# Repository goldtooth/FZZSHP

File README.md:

View this project on [CADLAB.io](https://cadlab.io/project/1550). 

# FZZSHP

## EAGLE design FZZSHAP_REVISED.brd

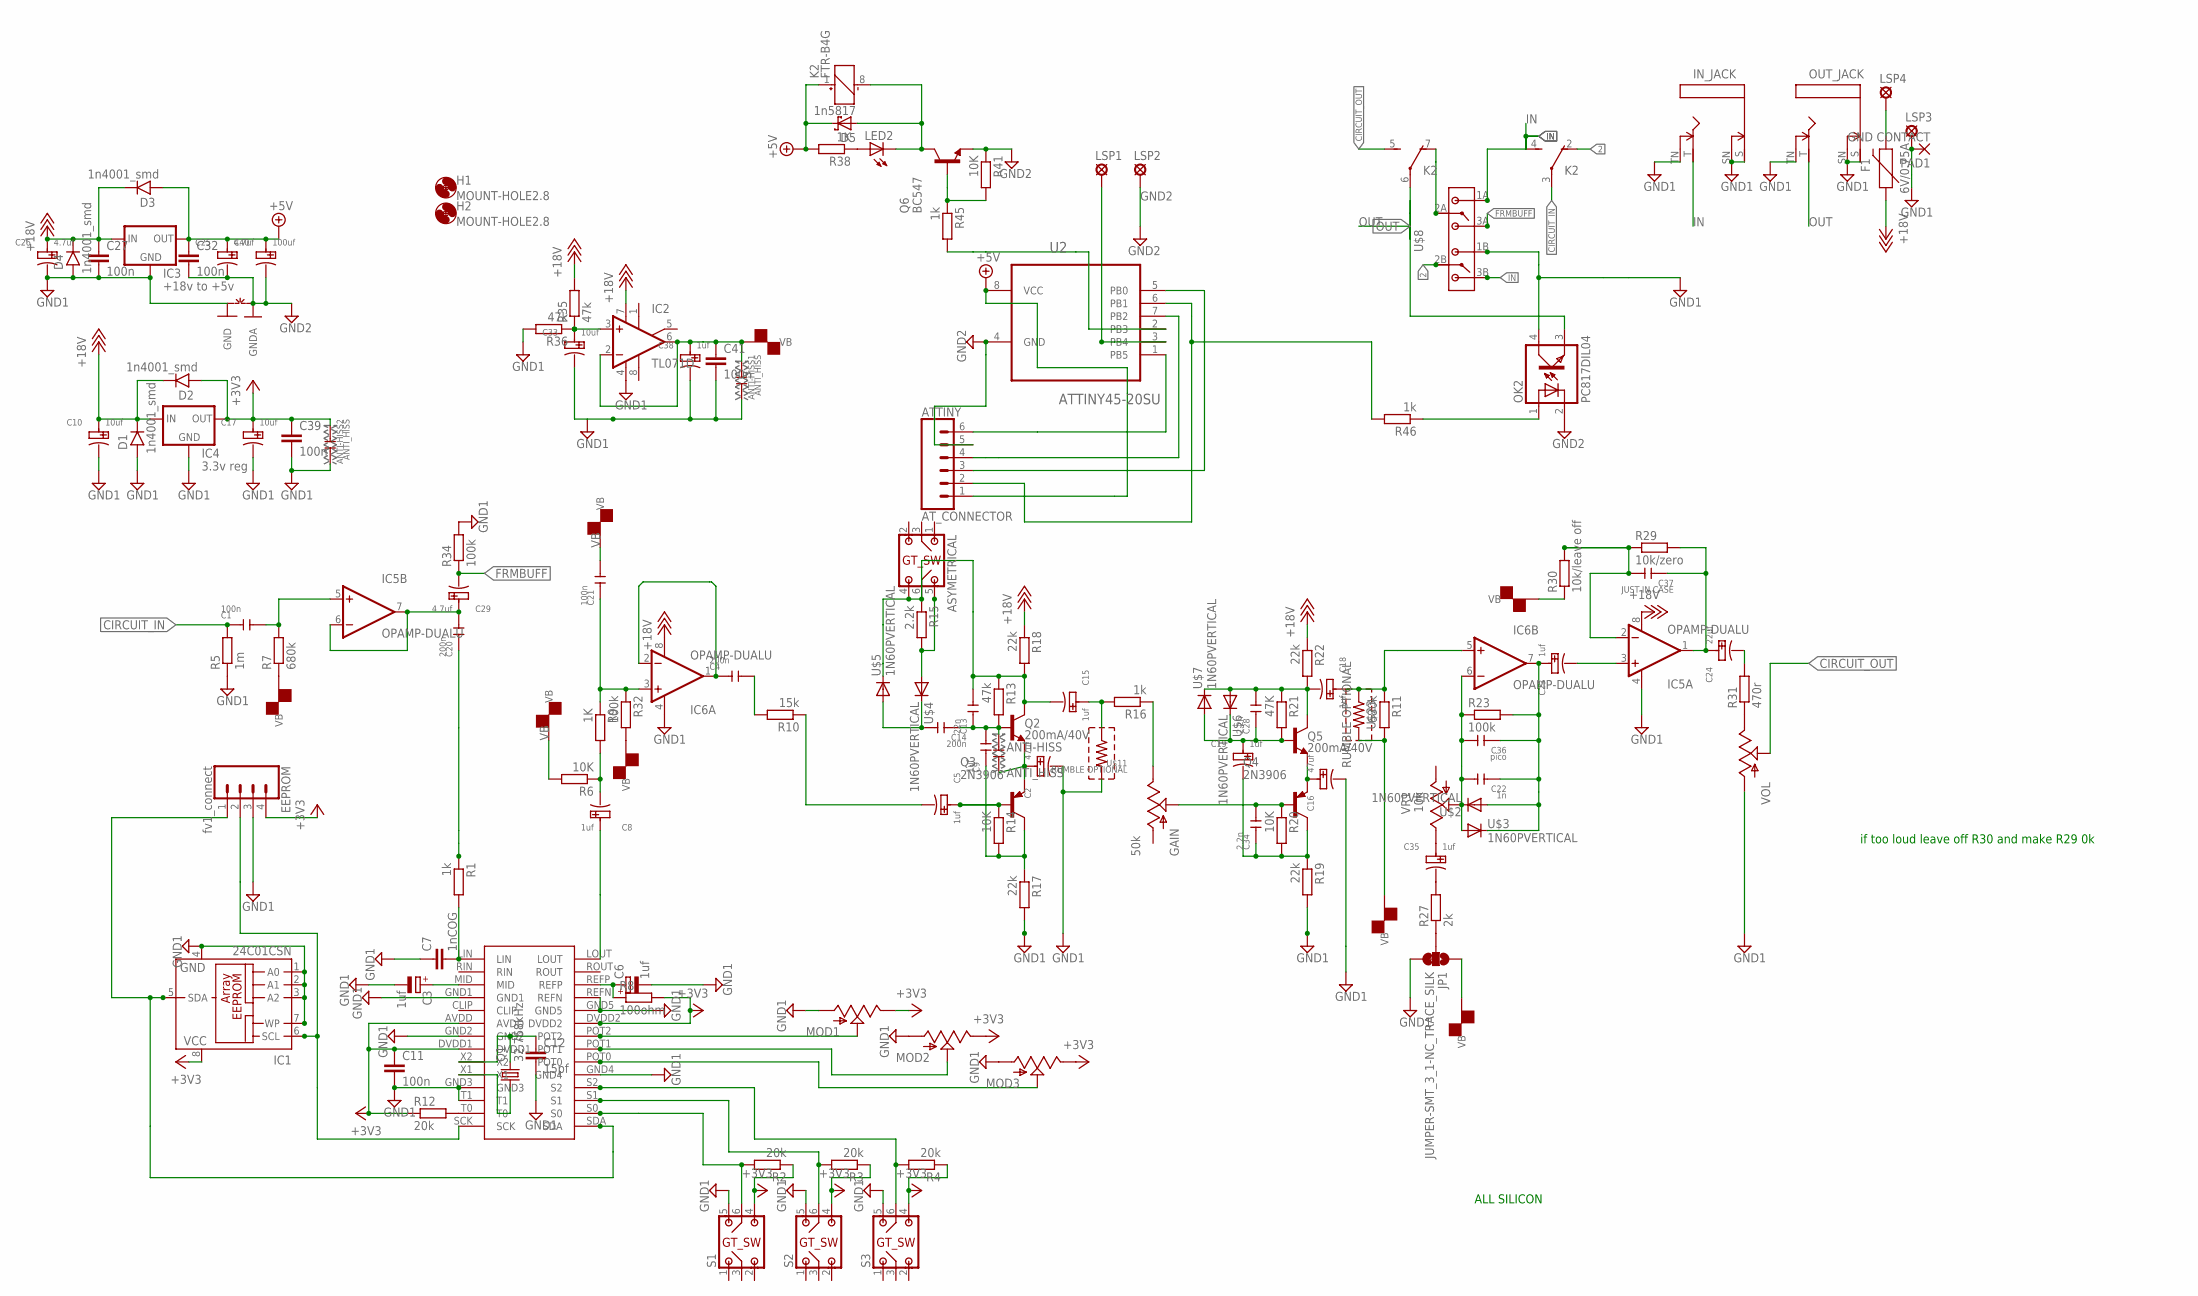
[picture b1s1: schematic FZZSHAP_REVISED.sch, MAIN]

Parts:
ANTI-HISS, ANTI-HISS1, ANTI-HISS2: ANTI_HISS; SMD_OPTIONAL
ASYMETRICAL: DP03SWPOT; DP-03
ATTINY: AT_CONNECTOR; 1X06_LONGPADS
C1, C21: 100n; CERAMIC-5MM
C2, C16: 47uf; PC-D5.3MM
C3, C6: 1uf; A/3216-18R
C4, C14, C20: 200n; CERAMIC-5MM
C5, C8, C15, C18, C19, C23, C35, C38: 1uf; PC-D5.3MM
C7: 1nCOG; C0805K
C9: 1uf; CERAMIC-5MM
C10, C17, C33: 10uf; PC-D5.3MM
C11: 100n; C0805
C12: 15pf; C0805
C13: 22n; CERAMIC-5MM
C22: 1n; CERAMIC-5MM
C24: 22uf; PC-D5.3MM
C25, C26, C29: 4.7uf; PC-D5.3MM
C27, C32, C39, C41: 100n; C1206
C28, C34: 2.2n; CERAMIC-5MM
C36: pico; CERAMIC-5MM
C37: JUST IN CASE; CERAMIC-5MM
C40: 100uf; PC-D5.3MM
D1, D2, D3, D4: 1n4001_smd; DO41-1
D5: 1n5817; SMB
EEPROM: fv1_connect; 1X04_LONGPADS
F1: 6V/0.75A; 1206
GAIN: 50k; SLIDER_PAC
H1, H2: MOUNT-HOLE2.8; 2,8
IC1: 24C01CSN; SO-08
IC2: TL071D; SO08
IC3: +18v to +5v; TO-252
IC4: 3.3v reg; SOT223
IC5, IC6: OPAMP-DUALU; SO08
IN_JACK: MMMONNN; MONO
JP1: JUMPER-SMT_3_1-NC_TRACE_SILK; SMT-JUMPER_3_1-NC_TRACE_SILK
K2: FTR-B4G
LED2: LED3MM
LSP1, LSP2, LSP3, LSP4: LSP10
MOD1, MOD2, MOD3: POTSLIDEY; SLIDER_PAC
OK2: PC817DIL04; SMD4
OUT_JACK: MMMONNN; MONO
PAD1: GND CONTACT; SMD2,54-5,08
Q1: 32.768kHz; CRYSTAL-TXC-7A
Q2, Q5: 200mA/40V; TO-92
Q3, Q4: 2N3906; TO92
Q6: BC547; TO92
R1, R16: 1k; R1206
R2, R3, R4, R12: 20k; R1206
R5: 1m; R1206
R6, R14, R20: 10K; R1206
R7, R11: 680k; R1206
R8: 100ohm; R1206
R9: 1K; R1206
R10: 15k; R1206
R13, R35, R36: 47k; R1206
R15: 2.2k; R1206
R17, R18, R19, R22: 22k; R1206
R21: 47K; R1206
R23, R32, R34: 100k; R1206
R27: 2k; R1206
R29: 10k/zero; R1206
R30: 10k/leave off; R1206
R31: 470r; R1206
R38: 1K; M1206
R41: 10K; M1206
R45, R46: 1k; M1206
S1, S2, S3: DP03SWPOT; DP-03
U2: ATTINY45-20SU; SOIC127P798X216-8N
U$1: FV-1SOIC28; SOIC28
U$2, U$3, U$4, U$5, U$6, U$7: 1N60PVERTICAL; DO41-1
U$8: BYSWITCH; BUFF/TRBYPASS
U$11, U$23: RUMBLE OPTIONAL; C1206
VOL: POTSLIDEY; SLIDER_PAC
VR1: 10k; 3223G
~NUDEV~1: GND-GNDA1,27MM; GND-GNDA-1,27MM

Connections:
2: K2.2 (O), U$8.2B
+3V3: ANTI-HISS2.1, C11.1, C17.+, C39.1, D2.A, EEPROM.4, IC1.8 (VCC), IC4.3 (OUT), MOD1.3 (E), MOD2.3 (E), MOD3.3 (E), R2.1, R3.1, R4.1, R8.2, R12.1, S1.4, S2.4, S3.4, U$1.AVDD, U$1.DVDD1, U$1.DVDD2
+5V: ATTINY.1, C25.+, C32.1, C40.+, D3.A, D5.C, IC3.2 (OUT), K2.1 (+), R38.2, U2.8 (VCC)
+18V: C10.+, C26.+, C27.1, D1.C, D2.C, D3.C, D4.C, F1.1, IC2.7 (V+), IC3.1 (IN), IC4.1 (IN), IC5.8 (V+), IC6.8 (V+), R18.1, R22.1, R35.2
CIRCUIT_IN: C1.1, K2.3, R5.2
CIRCUIT_OUT: K2.5 (S), VOL.2 (S)
FRMBUFF: C29.-, R34.1, U$8.3A
FV-1_SW_1: R2.2, S1.6 (5), U$1.S0
FV-1_SW_2: R3.2, S2.6 (5), U$1.S1
FV-1_SW_3: R4.2, S3.6 (5), U$1.S2
GND1: ANTI-HISS1.2, ANTI-HISS2.2, C2.-, C3.-, C6.-, C7.1, C10.-, C11.2, C12.2, C16.-, C17.-, C26.-, C27.2, C33.-, C38.-, C39.2, C41.2, D1.A, D4.A, EEPROM.3, IC1.1 (A0), IC1.2 (A1), IC1.3 (A2), IC1.4 (GND), IC1.7 (WP), IC2.4 (V-), IC3.3 (GND), IC4.2 (GND), IC4.4 (GND), IC5.4 (V-), IC6.4 (V-), IN_JACK.S, IN_JACK.SN, IN_JACK.TN, JP1.3, LSP3.MP, MOD1.1 (A), MOD2.1 (A), MOD3.1 (A), OK2.4 (COL), OUT_JACK.S, OUT_JACK.SN, OUT_JACK.TN, PAD1.1, R5.1, R17.2, R19.2, R34.2, R36.2, S1.5 (6), S2.5 (6), S3.5 (6), U$1.GND1, U$1.GND2, U$1.GND3, U$1.GND4, U$1.GND5, U$1.REFN, U$1.T1, U$8.1B, U$11.2, VOL.1 (A), ~NUDEV~1.GND
GND2: ATTINY.5, C25.-, C32.2, C40.-, LSP2.MP, OK2.2 (C), Q6.1 (E), R41.1, U2.4 (GND), ~NUDEV~1.GNDA
IN: IN_JACK.T, K2.4 (S), U$8.1A, U$8.3B
LEFT_IN: C20.1, R1.1
LEFT_OUT: C8.+, U$1.LOUT
unnamed: C5.+, Q3.2 (B), R14.1
unnamed: MOD3.2 (S), U$1.POT0
unnamed: C8.-, R6.1, R9.2
unnamed: C15.+, R16.2, U$11.1
unnamed: C1.2, IC5.5 (+IN), R7.2
unnamed: C4.2, R10.2
unnamed: C5.-, R10.1
unnamed: C21.1, IC6.3 (+IN), R9.1, R32.1
unnamed: C4.1, IC6.1 (OUT), IC6.2 (-IN)
unnamed: ASYMETRICAL.5 (6), R15.2, U$4.A
unnamed: C37.2, IC5.2 (-IN), R29.1, R30.2
unnamed: C35.+, VR1.3 (E)
unnamed: MOD2.2 (S), U$1.POT1
unnamed: ANTI-HISS.2, C2.+, Q2.1 (E), Q3.3 (E)
unnamed: ASYMETRICAL.4, ASYMETRICAL.6 (5), C13.2, C15.-, Q2.3 (C), R13.1, R15.1, R18.2, U$5.C
unnamed: GAIN.3 (E), R16.1
unnamed: C9.1, Q3.1 (C), R14.2, R17.1
unnamed: MOD1.2 (S), U$1.POT2
unnamed: C18.+, IC6.5 (+IN), R11.1, U$23.1
unnamed: C23.-, IC5.3 (+IN)
unnamed: C22.1, C23.+, C36.1, IC6.7 (OUT), R23.2, U$2.A, U$3.C
unnamed: C35.-, R27.2
unnamed: C16.+, Q4.3 (E), Q5.1 (E)
unnamed: EEPROM.2, IC1.6 (SCL), U$1.SCK
unnamed: C24.+, C37.1, IC5.1 (OUT), R29.2
unnamed: EEPROM.1, IC1.5 (SDA), U$1.SDA
unnamed: C34.2, GAIN.2 (S), Q4.2 (B), R20.1
unnamed: C7.2, R1.2, U$1.LIN
unnamed: C19.+, C28.1, Q5.2 (B), R21.2, U$6.C, U$7.A
unnamed: C14.2, U$4.C, U$5.A
unnamed: C3.+, U$1.MID
unnamed: F1.2, LSP4.MP
unnamed: C19.-, C34.1, Q4.1 (C), R19.1, R20.2
unnamed: C24.-, R31.2
unnamed: JP1.2, R27.1
unnamed: C22.2, C36.2, IC6.6 (-IN), R23.1, U$2.C, U$3.A, VR1.2 (S)
unnamed: C33.+, IC2.3 (+IN), R35.1, R36.1
unnamed: ANTI-HISS.1, C9.2, C13.1, C14.1, Q2.2 (B), R13.2
unnamed: C20.2, C29.+, IC5.6 (-IN), IC5.7 (OUT)
unnamed: R31.1, VOL.3 (E)
unnamed: C6.+, R8.1, U$1.REFP
unnamed: C18.-, C28.2, Q5.3 (C), R21.1, R22.2, U$6.A, U$7.C
unnamed: R12.2, U$1.T0
unnamed: C12.1, Q1.P$2 (2), U$1.X2
unnamed: Q1.P$1 (1), U$1.X1
unnamed: K2.7 (O), U$8.2A
unnamed: ATTINY.3, U2.5 (PB0)
unnamed: ATTINY.2, R46.2, U2.6 (PB1)
unnamed: ATTINY.4, U2.7 (PB2)
unnamed: ATTINY.6, U2.1 (PB5)
unnamed: LED2.A, R38.1
unnamed: D5.A, K2.8 (-), LED2.K (C), Q6.3 (C)
unnamed: Q6.2 (B), R41.2, R45.1
unnamed: R45.2, U2.2 (PB3)
unnamed: LSP1.MP, U2.3 (PB4)
unnamed: OK2.1 (A), R46.1
OUT: K2.6, OK2.3 (EMIT), OUT_JACK.T
VB: ANTI-HISS1.1, C21.2, C38.+, C41.1, IC2.2 (-IN), IC2.6 (OUT), JP1.1, R6.2, R7.1, R11.2, R30.1, R32.2, U$23.2

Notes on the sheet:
ALL SILICON
if too loud leave off R30 and make R29 0k

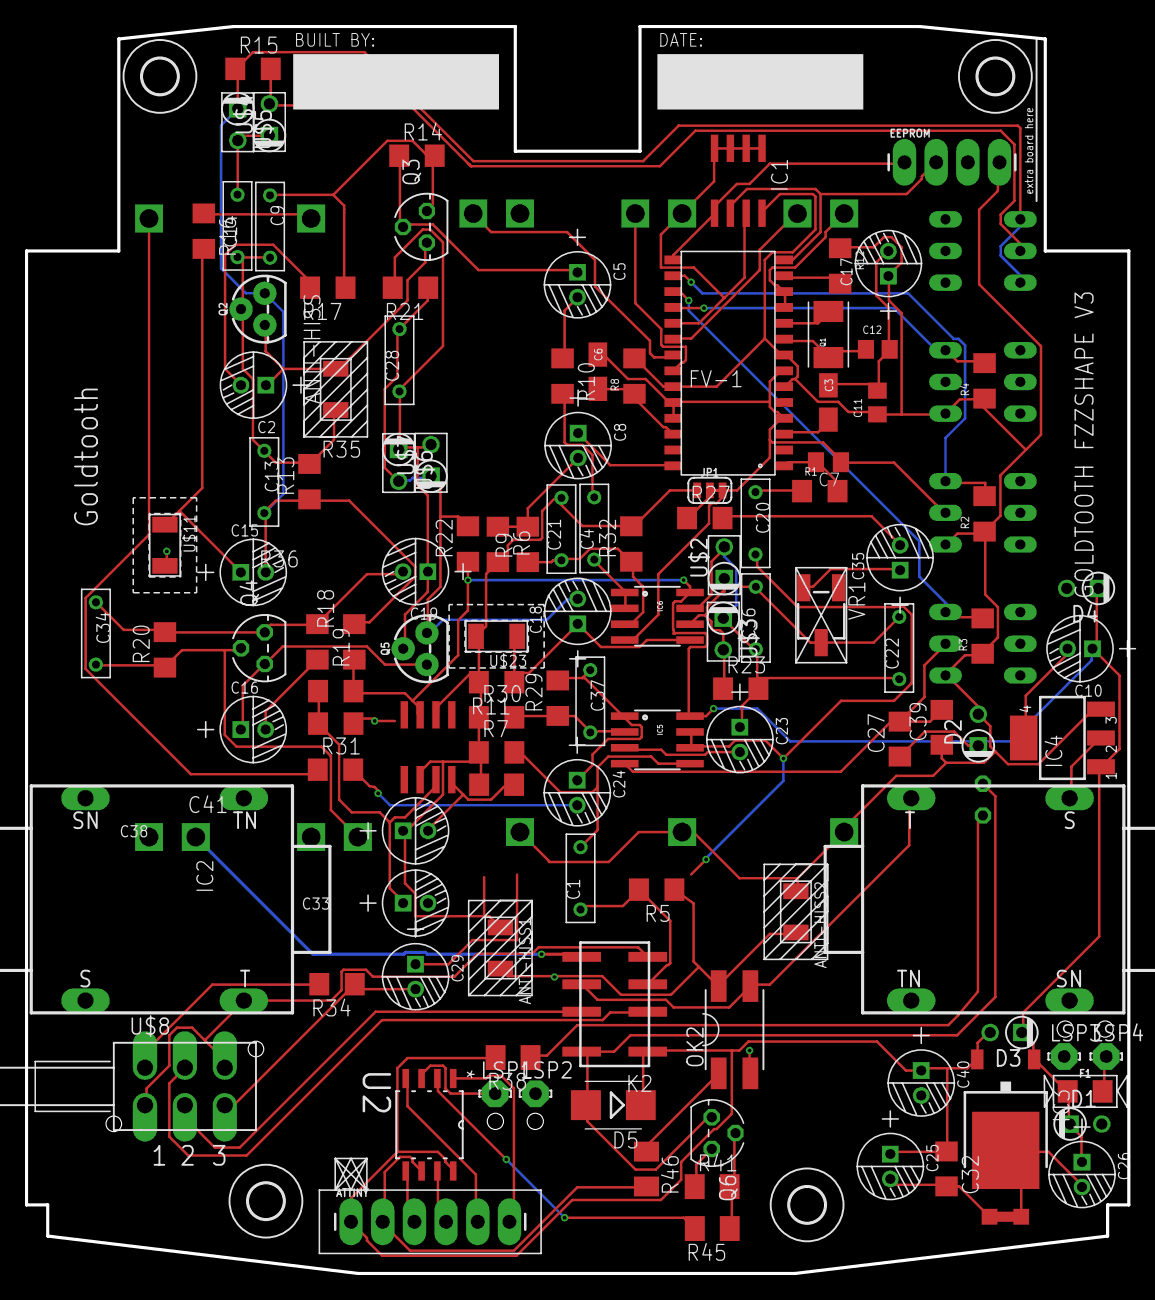
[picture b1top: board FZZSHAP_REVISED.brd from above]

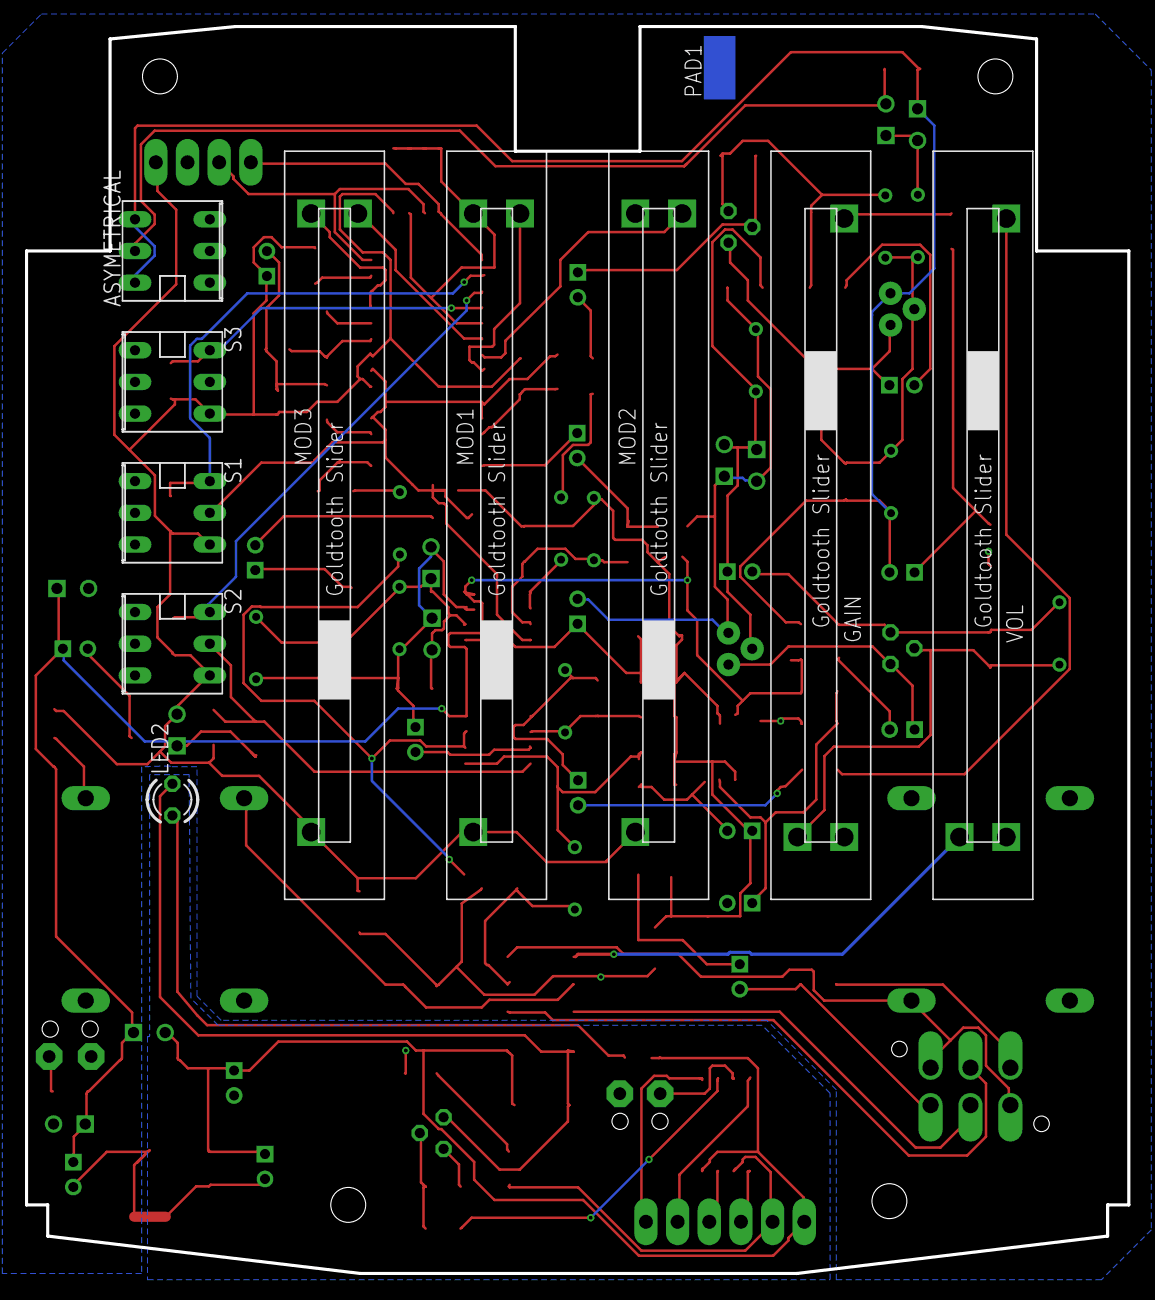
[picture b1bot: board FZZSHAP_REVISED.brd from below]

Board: 2 copper layers, 88.4 x 100.0 mm, 138 parts (11 on the bottom side), 73 nets.

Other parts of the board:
H3, H4: MOUNT-HOLE2.8; 2,8
U$17, U$18, U$19, U$20: HOLD

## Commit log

2019-01-07 fzz
    fzz
2019-01-07 Rename .gotignore to .gitignore
2019-01-07 removed
2019-01-07 s
    s
2019-01-07 Backlink to CADLAB.io has been added.

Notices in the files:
parts and their libraries:
SparkFun-FreqCtrl: Licensing: CC v3.0 Share-Alike You are welcome to use this library for commercial purposes.
SparkFun-DiscreteSemi: Licensing: Creative Commons ShareAlike 4.0 International - https://creativecommons.org/licenses/by-sa/4.0
